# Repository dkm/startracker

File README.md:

# Electronic
- [X] prototype on breadboard:
  - [X] power motor and arduino from 12V
  - [X] use button and endstop to do a reset
- [X] finish PCB design
- [X] create PCB (engrave, drill, solder)
- [X] test PCB

# 3D printing

## gears
- [X] remodel gears
- [X] print gears
- [X] test gears

## laser
- [X] remodel laser holder
- [X] print laser holder
- [X] test laser holder : Laser not powerful enough

## rod holder
- [X] remodel rod holder
- [X] print rod holder
- [X] test rod holder

## model a box
- [ ] model a box
- [ ] print box
- [ ] assemble/test box

# Mecanics
- [X] plan for assembly
- [X] assemble

# Software
- [X] first proto that only drive the gear
- [X] second proto that can do reset

# general
- [X] test : works, but still some fine tuning to do.

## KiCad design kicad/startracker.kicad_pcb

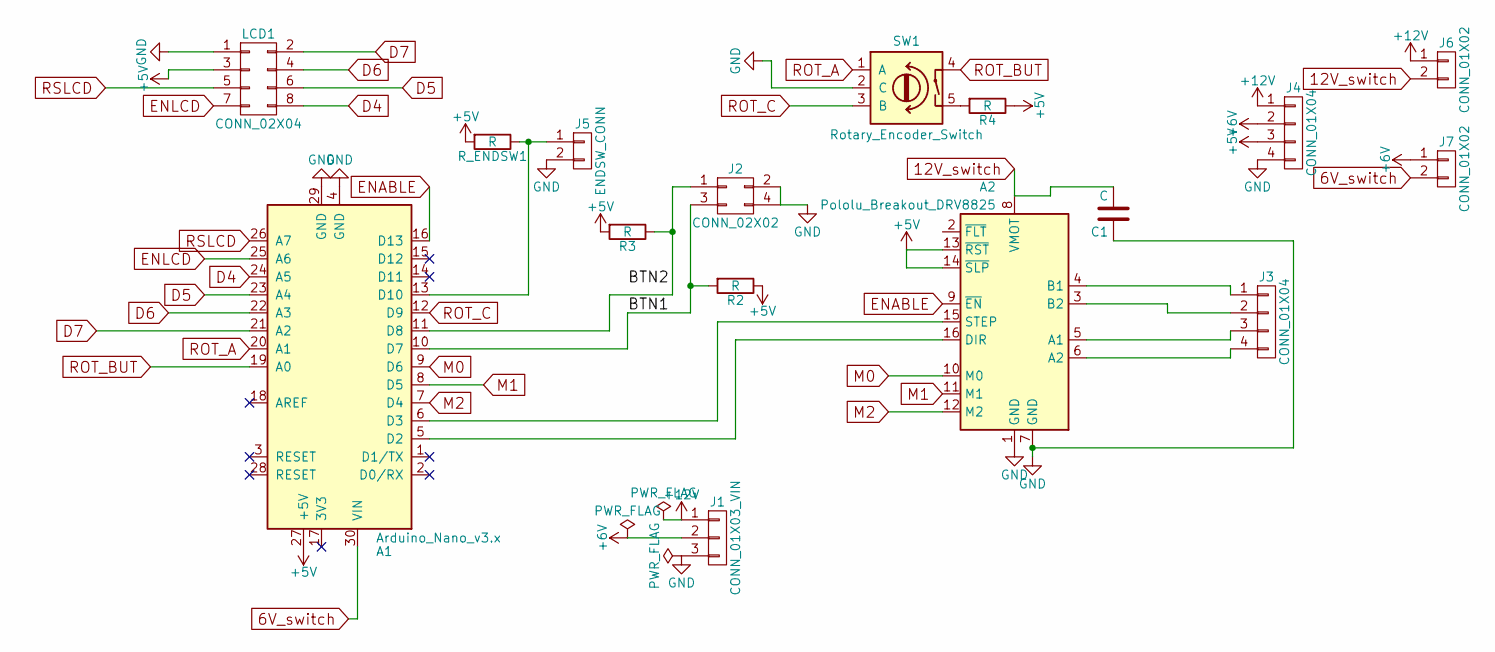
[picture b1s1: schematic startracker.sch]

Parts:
A1: Arduino_Nano_v3.x; Arduino_Nano_WithMountingHoles
A2: Pololu_Breakout_DRV8825; Pololu_Breakout-16_15.2x20.3mm
C1: C; C_Radial_D8_L11.5_P3.5
J1: CONN_01X03_VIN; JST_PH_B3B-PH-K_03x2.00mm_Straight
J2: CONN_02X02; Pin_Header_Straight_2x02
J3, J4: CONN_01X04; Pin_Header_Straight_1x04
J5: ENDSW_CONN; Pin_Header_Straight_1x02
J6, J7: CONN_01X02; Pin_Header_Straight_1x02
LCD1: CONN_02X04; Pin_Header_Straight_2x04
R2, R3, R4: R; Resistor_Horizontal_RM7mm
R_ENDSW1: R; Resistor_Horizontal_RM7mm
SW1: Rotary_Encoder_Switch; SF-ROTARY-ENCODER

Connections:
6V_switch: A1.30 (VIN), J7.2
12V_switch: A2.8 (VMOT), C1.2, J6.2
+5V: A1.27 (+5V), A2.13 (~RST), A2.14 (~SLP), J4.3, LCD1.3, R2.1, R3.2, R4.1, R_ENDSW1.2
+6V: J1.2, J4.2, J7.1
+12V: J1.1, J4.1, J6.1
/BTN1: A1.10 (D7), J2.3, R2.2
D4: A1.24 (A5), LCD1.8
D5: A1.23 (A4), LCD1.6
D6: A1.22 (A3), LCD1.4
D7: A1.21 (A2), LCD1.2
ENABLE: A1.16 (D13), A2.9 (~EN)
ENLCD: A1.25 (A6), LCD1.7
GND: A1.4 (GND), A1.29 (GND), A2.1 (GND), A2.7 (GND), C1.1, J1.3, J2.2, J2.4, J4.4, J5.2, LCD1.1, SW1.2 (C)
M0: A1.9 (D6), A2.10 (M0)
M1: A1.8 (D5), A2.11 (M1)
M2: A1.7 (D4), A2.12 (M2)
unnamed: A1.5 (D2), A2.16 (DIR)
unnamed: A1.6 (D3), A2.15 (STEP)
unnamed: A1.11 (D8), J2.1, R3.1
unnamed: A1.13 (D10), J5.1, R_ENDSW1.1
unnamed: A2.3 (B2), J3.2
unnamed: A2.4 (B1), J3.1
unnamed: A2.5 (A1), J3.3
unnamed: A2.6 (A2), J3.4
unnamed: R4.2, SW1.5
ROT_A: A1.20 (A1), SW1.1 (A)
ROT_BUT: A1.19 (A0), SW1.4
ROT_C: A1.12 (D9), SW1.3 (B)
RSLCD: A1.26 (A7), LCD1.5

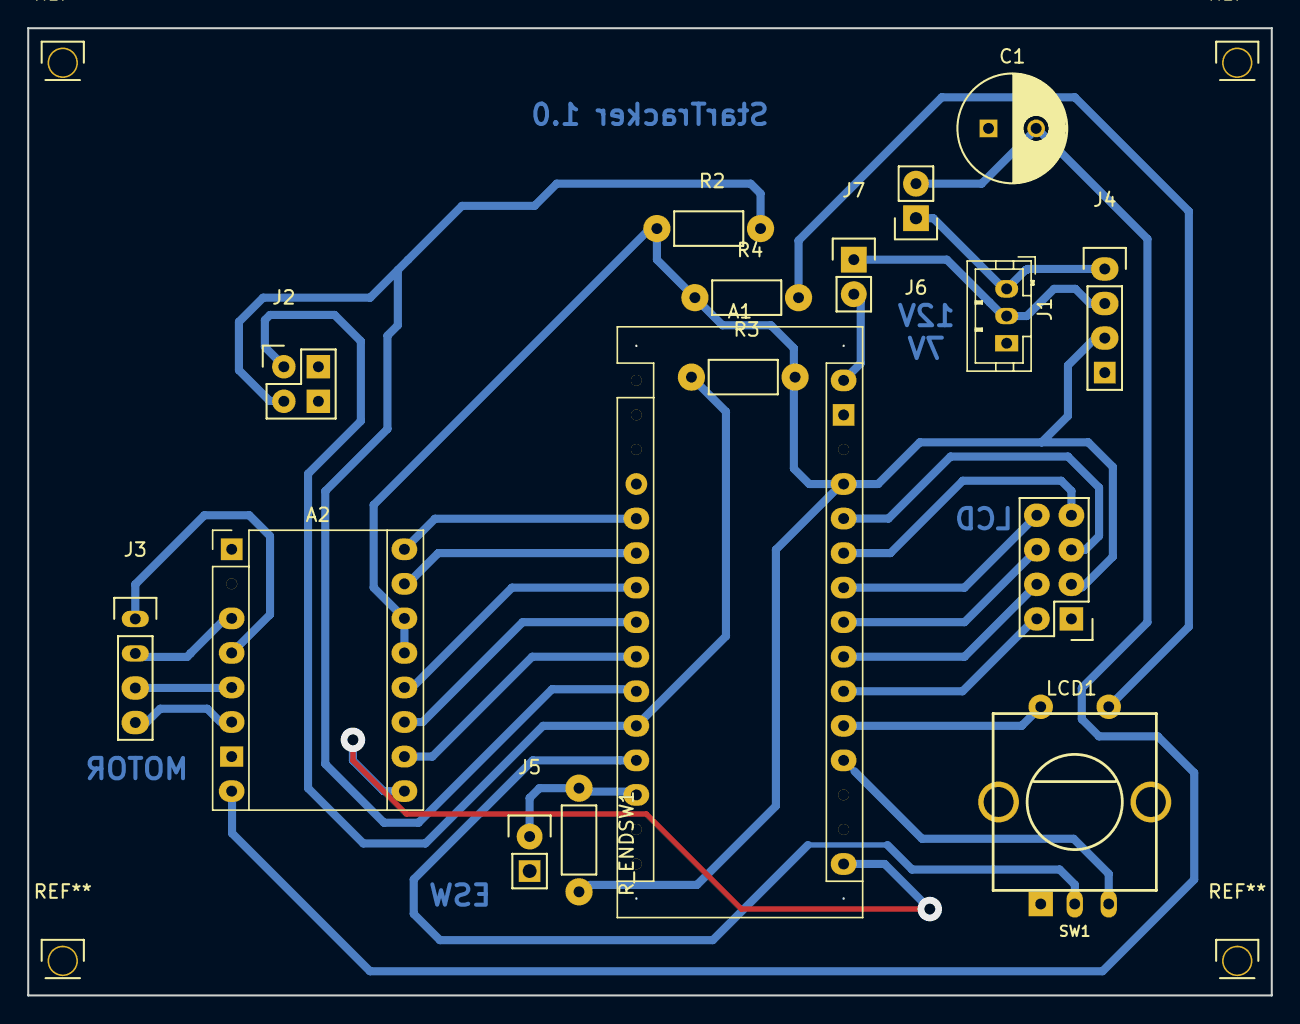
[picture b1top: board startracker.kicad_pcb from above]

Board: 2 copper layers, 91.4 x 71.1 mm, 16 parts (0 on the bottom side), 29 nets.

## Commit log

2017-05-15 first kicad draft
2017-05-15 sample arduino sketch for testing nema17
2017-05-16 making progress on elec sch
2017-05-19 add some footprint, still some issue with some components
2017-05-20 first pcb routed on single layer
2017-05-23 add 7.5V connector
2017-05-23 refresh project files
2017-05-24 started modifying code from jjrobots
2017-05-29 PCB fix
2017-06-02 refresh pcb
2017-06-08 new pcb version
2017-06-08 add automata skel
2017-06-08 use StepperDriver lib
2017-06-08 use timer1 and use makefile
    use timer1 (initial code)
    use makefile instead of arduino IDE.
2017-06-08 add submodule with footprint libs
2017-06-08 update board : use enable, m0, ...
2017-06-09 reworked elec schema + pcb
2017-06-11 initial work for computing rotation
2017-06-13 check routine in C++ and python
2017-06-14 rework float computation
    looks like the arduino float is not a good fit for this one: results are
    diverging after few seconds. Fallback to some hardcoded numerical
    values.
    known problem: timer does not tick periodically
2017-06-15 3D models for gears
2017-06-15 fix angle compute + use millis
2017-06-16 README + tasks
2017-06-19 enl4rge gear shaft hole
2017-06-19 add nema17 holder plate
2017-06-20 some cleaning + initial code for reset position
    remove dead code commented out
    initial routine for reseting position on long press
2017-06-20 update current state
2017-06-21 add rod cover model
    used to cover screws around rod and allow for big gear to turn.
2017-06-21 initial work for laster holder
2017-06-21 add endstrop down to pcb
2017-06-22 minor changes in PCB
    add drill hole in corners
    make all GND pad rectangular
    add labels for connectors
2017-06-22 PCB cleanups
    larger track size, add spacing when possible.
2017-06-23 add switch connectors for both pwr (12 and 7)
    both can be shorted for using only 12V.
2017-06-23 Add Switch submodule for arduino
    Switch module can be used to debounce push buttons
2017-06-23 Add simple debug routine
2017-06-23 ask emacs to use c++ mode for the .ino
2017-06-23 control automata basics
    start in IDLE.
    IDLE :: 1 press => RUN ; 2 press => RESET
    RUN :: 1 press => IDLE
    RESET :: end_stop => IDLE
    Stepper direction can be changed.
    Stepper microstepping can be changed.
2017-06-23 Laser holder work
    Hook size nearly good
2017-06-23 Add 3D model for stepper cover
2017-06-25 add weak debug routines + better state change traces
2017-06-25 code cleaning + add startup state
    remove unused code, add startup state.
2017-06-25 change microstepping config and rotation freq
    microstepping 2->16
    freq: 0.5Hz -> 5Hz
2017-06-25 refresh config code for stepper direction
2017-06-25 minor changes in PCB
    rework edge cut, refresh some tracks/drill holes.
2017-06-25 add box model (from the Ultimate Box Maker)
    http://heartygfx.blogspot.com
    OpenScad Parametric Box
    CC BY-NC 3.0 License
2017-06-25 model for Dolica tripod quick release mount.
    prepare for 4 M3 screws/hexnuts.
2017-06-25 add initial box model
    Based on Ultimate Box Maker
    https://www.thingiverse.com/thing:1264391
2017-06-26 laser holder nearly ready
2017-06-29 fine tune nut holes in laser holder
2017-07-02 change DRV8825 mode pins
    for easier routing, mode pins have swapped.
2017-07-02 update with latest steps
2017-07-02 fine tune laser holder
    now, radius may be a bit too large, but at least, the print does not
    brake when fiting laser in place.
2017-07-02 remove old file for box
2017-07-04 helper to keep scad and arduino values in sync
    - run teeth_config.sh to sync scad values from gears in arduino code.
    - small reindent
2017-07-06 code cleanup and better trace output.
2017-07-06 disable button 2 and 3
    not yet used and leftover setup conflicts with mode pin for stepper driver.
2017-07-06 use same time measure for whole function
    should have minor impact, but use same time value for all computation.
2017-07-06 minor change in 'native' checker
    use correct gears sizes.
2017-07-09 new debug level, change timer arith
    Use a 'moderate' debug level: can have impact on behavior, but is
    still human readable without buffer.
    Use unsigned arith for timer handling and check for underflow.
2017-07-11 box: add mounting slot
2017-07-12 box: switch and button holes
2017-07-14 cleanup + more helpfull debug trace
2018-02-24 use submodule for arduino makefile
2018-02-24 initial end stop holder. WIP
2018-02-25 update end stop model, still not OK
    too tight, nothing fits correctly.
2018-02-28 add margin for both the plate grip and end stop location.
2018-05-05 arduino: smoother movements
    increase microstep, reduce lib's RPM and increase freq
2018-05-05 Add comments
    Add comments in makefile. I had to work a bit in order to remember how
    things work; help future me by not having to redo this work again.
    Clean a bit the .ino header. This was all based on jjrobots work, but it
    has been all changed since.
2018-05-05 bump arduino-makefile rev to latest master.
2018-05-05 Bump StepperDriver rev
2018-05-12 Do not build debug code
2018-05-13 minor makefile tuning
    Allow for ARDUINO_DIR variable override.
2018-05-13 Relax math precision and let GCC be more agressive
    Use -ffast-math for building C/C++. We don't need to be exact, let GCC
    be more agressive and saves few bytes (currently it saves 80bytes).
2018-05-13 move config in dedicated file, fix initial setup/reset
    Move all user-modifiable variables in config.h. User should only need
    to change items in this file.
    Fix initial setup of the tracker. The initial angle depends on the
    specific build.
2018-05-30 add holder for new laser (laser 301)
2018-09-16 Add rod holder model, replaces the one from jj robots that is not slic3r friendly
    Original work from Clément Leger : https://github.com/clementleger/3d_parts/blob/master/projector_lifter/adjustable_mount.scad
2019-01-20 enl4rge rod holder h0l3
2019-05-04 refresh gears after move away from aluminium plate
    With the wood board replacing the alumnium plate, I need to have
    both gears with the same support.
2019-05-22 make big gears rim margin larger
    With a 0 margin, it's not possible to fit the gear because of the
    motor screw.
2019-07-06 Flip gears
    My threaded rod was mounted in the other side, so if I want the gears
    to turn in the correct direction, I have to flip them :)
2019-07-14 Add missing slide parts from JJrobots
    Original file can be found here : https://www.thingiverse.com/thing:974906/files
    Licensed CC-A
    Add brief for files pulled from other projects.
2019-07-17 Change motor shaft diameter
    Looks like printing with good printer makes this hole too large.
    The captive nut then pushes the shaft when thightened unevenly,
    ending up with the gear not turning around the shaft correctly.
2019-07-17 Refine the parameters for having nive arcs
    Set the $fn some some hage value (maybe a bit overkill) so the facets
    are less visible and hopefully the gears smoother.
2019-08-17 bump thirdparty dep version
2019-08-17 Change default arduino SDK version
    Change from 1.8.5 to 1.8.9
2019-08-22 Allow for working with gravity instead of against it
    The hinge_opening config can be used for setup where the hinge is
    closing when working instead of opening.
2019-08-25 Fix init and hinge closing mode
    Init and hinge closing mode were completely wrong.
2019-08-28 add needed var for upload target
